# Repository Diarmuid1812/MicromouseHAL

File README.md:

# MicromouseHAL

1. Link do dokumentu Overleaf - Roboty Mobilne etap 2 (bez edycji)
   https://www.overleaf.com/read/mfgwrnbxdtrh
   
2. Link do dokumentu Overleaf - Sterowniki Robotów etap 2 (bez edycji)
   https://www.overleaf.com/read/fxndmzvgxdkn

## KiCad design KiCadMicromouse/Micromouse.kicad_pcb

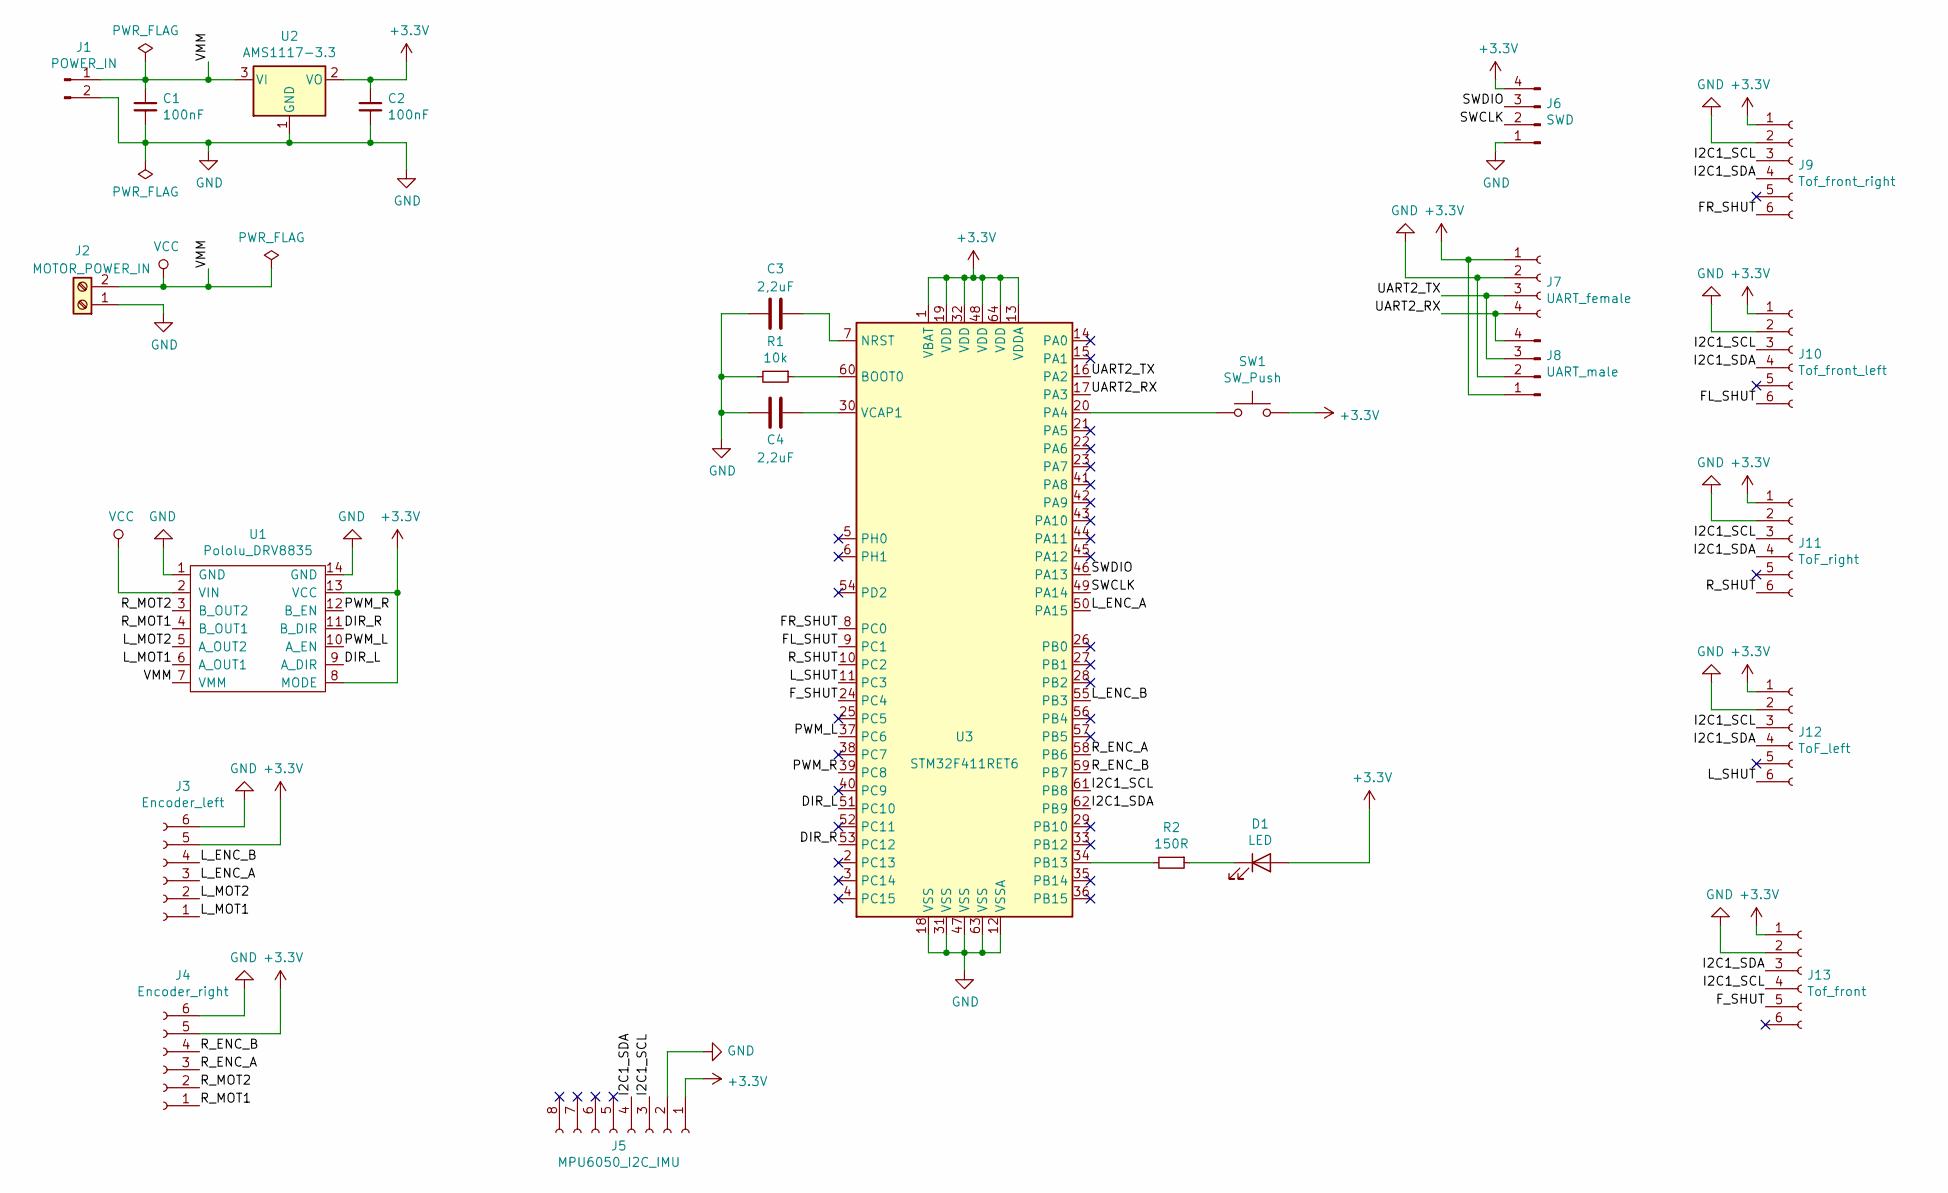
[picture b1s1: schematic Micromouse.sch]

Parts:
C1, C2: 100nF; C_1206_3216Metric
C3, C4: 2,2uF; C_1206_3216Metric
D1: LED; LED_D3.0mm
J1: POWER_IN; PinHeader_1x02_P2.54mm_Vertical
J2: MOTOR_POWER_IN; TerminalBlock_bornier-2_P5.08mm
J3: Encoder_left; PinSocket_1x06_P2.54mm_Vertical
J4: Encoder_right; PinSocket_1x06_P2.54mm_Vertical
J5: MPU6050_I2C_IMU; PinSocket_1x08_P2.54mm_Vertical
J6: SWD; PinHeader_1x04_P2.54mm_Vertical
J7: UART_female; PinSocket_1x04_P2.54mm_Vertical
J8: UART_male; PinHeader_1x04_P2.54mm_Vertical
J9: Tof_front_right; PinSocket_1x06_P2.54mm_Vertical
J10: Tof_front_left; PinSocket_1x06_P2.54mm_Vertical
J11: ToF_right; PinSocket_1x06_P2.54mm_Vertical
J12: ToF_left; PinSocket_1x06_P2.54mm_Vertical
J13: Tof_front; PinSocket_1x06_P2.54mm_Vertical
R1: 10k; R_1206_3216Metric
R2: 150R; R_1206_3216Metric
SW1: SW_Push; SW_SPST_TL3342
U1: Pololu_DRV8835; Pololu_DRV8835_rev
U2: AMS1117-3.3; SOT-223-3_TabPin2
U3: STM32F411RET6; LQFP-64_10x10mm_P0.5mm

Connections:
+3V3: C2.1, D1.2 (A), J3.5, J4.5, J5.1, J6.4, J7.1, J8.1, J9.1, J10.1, J11.1, J12.1, J13.1, SW1.2, U1.8 (MODE), U1.13 (VCC), U2.2 (VO), U3.1 (VBAT), U3.13 (VDDA), U3.19 (VDD), U3.32 (VDD), U3.48 (VDD), U3.64 (VDD)
/DIR_L: U1.9 (A_DIR), U3.51 (PC10)
/DIR_R: U1.11 (B_DIR), U3.53 (PC12)
/FL_SHUT: J10.6, U3.9 (PC1)
/FR_SHUT: J9.6, U3.8 (PC0)
/F_SHUT: J13.5, U3.24 (PC4)
/I2C1_SCL: J5.3, J9.3, J10.3, J11.3, J12.3, J13.4, U3.61 (PB8)
/I2C1_SDA: J5.4, J9.4, J10.4, J11.4, J12.4, J13.3, U3.62 (PB9)
/L_ENC_A: J3.3, U3.50 (PA15)
/L_ENC_B: J3.4, U3.55 (PB3)
/L_MOT1: J3.1, U1.6 (A_OUT1)
/L_MOT2: J3.2, U1.5 (A_OUT2)
/L_SHUT: J12.6, U3.11 (PC3)
/PWM_L: U1.10 (A_EN), U3.37 (PC6)
/PWM_R: U1.12 (B_EN), U3.39 (PC8)
/R_ENC_A: J4.3, U3.58 (PB6)
/R_ENC_B: J4.4, U3.59 (PB7)
/R_MOT1: J4.1, U1.4 (B_OUT1)
/R_MOT2: J4.2, U1.3 (B_OUT2)
/R_SHUT: J11.6, U3.10 (PC2)
/SWCLK: J6.2, U3.49 (PA14)
/SWDIO: J6.3, U3.46 (PA13)
/UART2_RX: J7.4, J8.4, U3.17 (PA3)
/UART2_TX: J7.3, J8.3, U3.16 (PA2)
GND: C1.2, C2.2, C3.2, C4.2, J1.2, J2.1, J3.6, J4.6, J5.2, J6.1, J7.2, J8.2, J9.2, J10.2, J11.2, J12.2, J13.2, R1.2, U1.1 (GND), U1.14 (GND), U2.1 (GND), U3.12 (VSSA), U3.18 (VSS), U3.31 (VSS), U3.47 (VSS), U3.63 (VSS)
unnamed: C3.1, U3.7 (NRST)
unnamed: C4.1, U3.30 (VCAP1)
unnamed: D1.1 (K), R2.1
unnamed: R1.1, U3.60 (BOOT0)
unnamed: R2.2, U3.34 (PB13)
unnamed: SW1.1, U3.20 (PA4)
VCC: C1.1, J1.1, J2.2, U1.2 (VIN), U1.7 (VMM), U2.3 (VI)

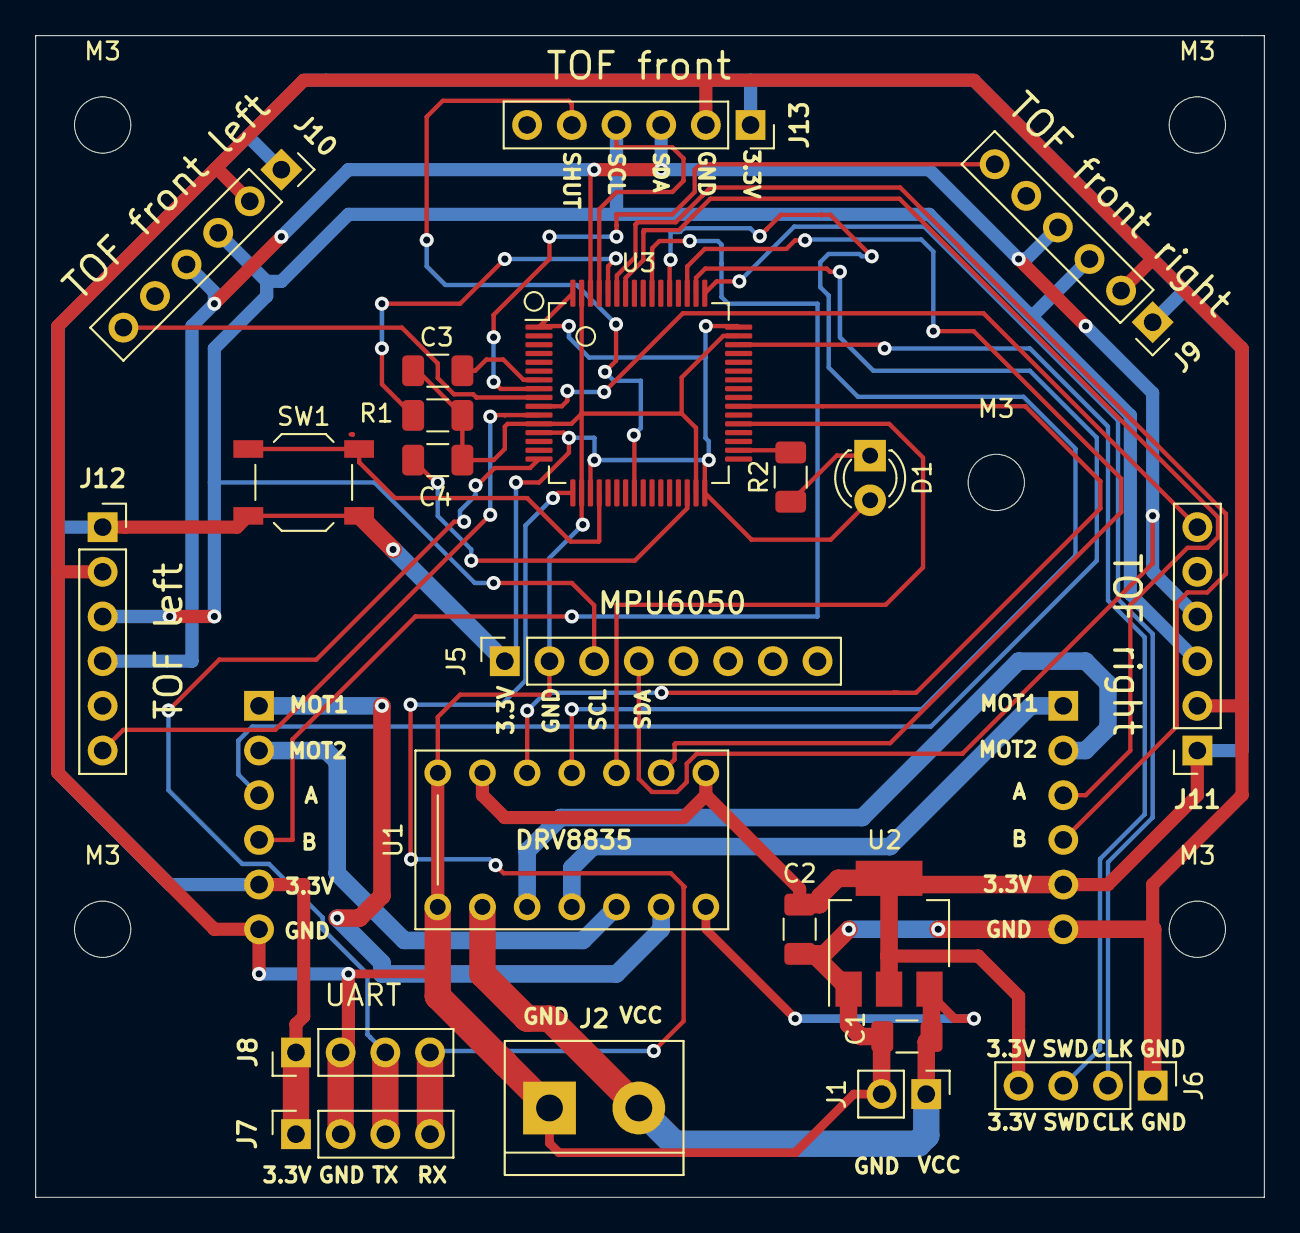
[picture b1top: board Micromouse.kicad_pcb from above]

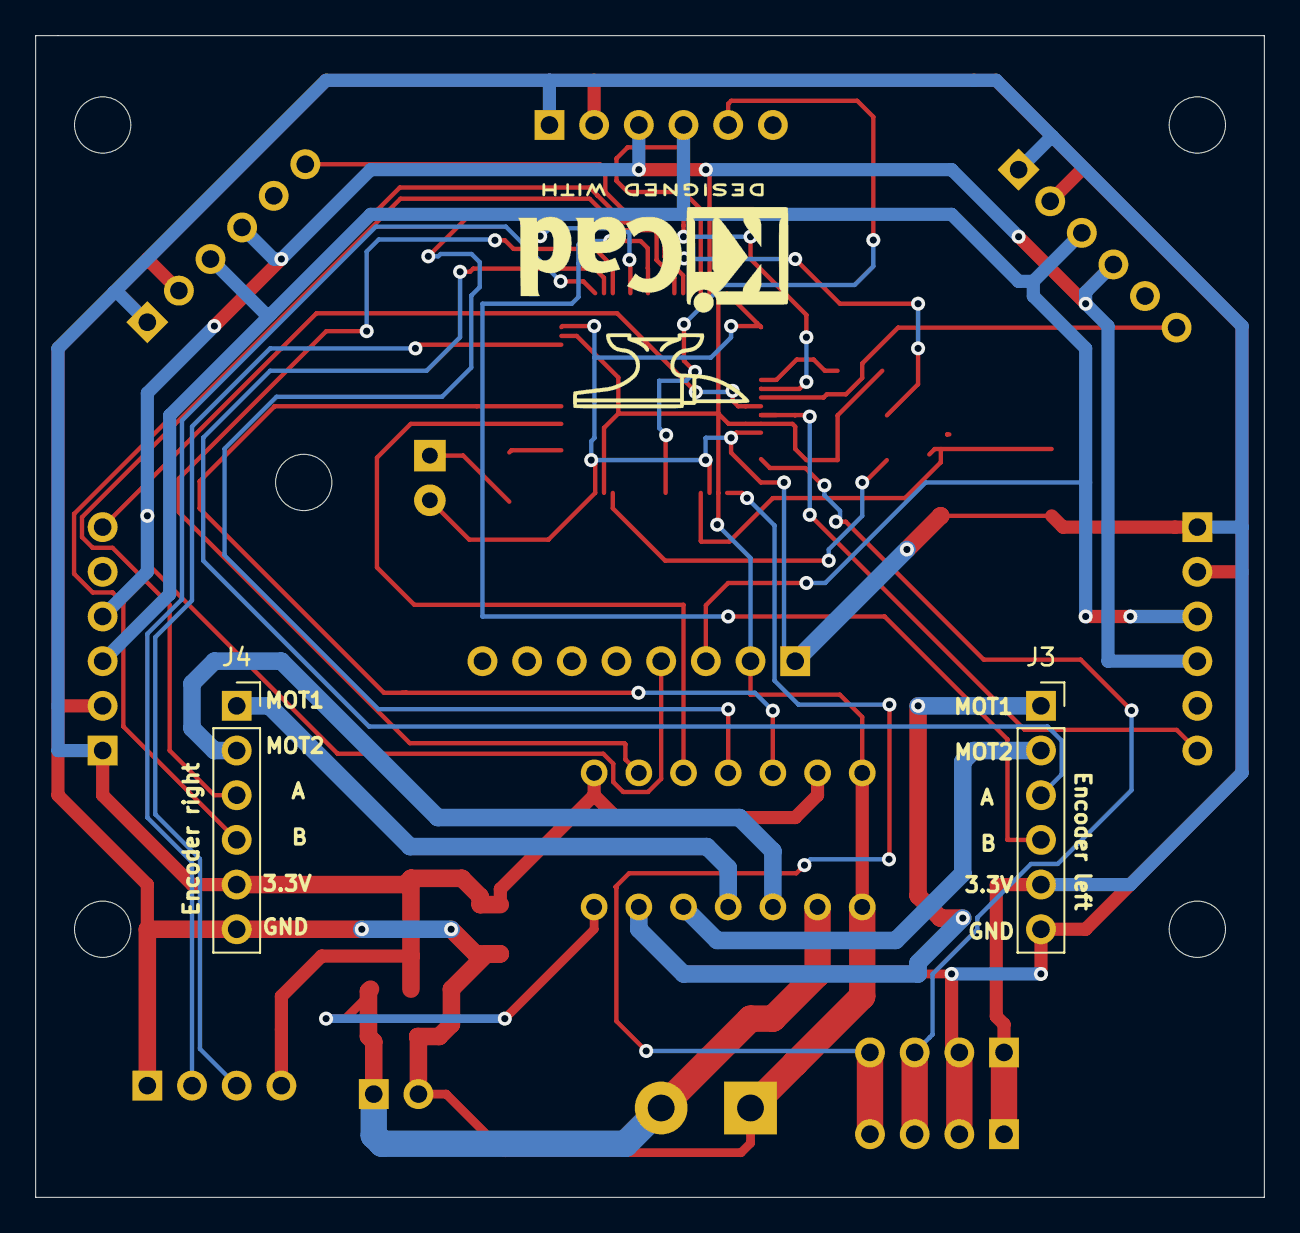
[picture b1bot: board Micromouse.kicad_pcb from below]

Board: 2 copper layers, 69.9 x 66.0 mm, 29 parts (2 on the bottom side), 32 nets.

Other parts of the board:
M3, M3#2, M3#3, M3#4, M3#5: MountingHole_3.2mm_M3

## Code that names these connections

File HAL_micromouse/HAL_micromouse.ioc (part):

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Mcu.Name=STM32F411R(C-E)Tx
Mcu.Package=LQFP64
Mcu.UserName=STM32F411RETx
PA13.GPIOParameters=GPIO_Label
PA13.GPIO_Label=TMS
PA13.Mode=Serial_Wire
PA13.Signal=SYS_JTMS-SWDIO
PA14.GPIOParameters=GPIO_Label
PA14.GPIO_Label=TCK
PA14.Mode=Serial_Wire
PA14.Signal=SYS_JTCK-SWCLK
PA15.GPIOParameters=GPIO_Label
PA15.GPIO_Label=ENC_L_A
PA15.Signal=S_TIM2_CH1_ETR
PA2.GPIOParameters=GPIO_Label
PA2.GPIO_Label=USART_TX
PA2.Mode=Asynchronous
PA2.Signal=USART2_TX
PA3.GPIOParameters=GPIO_Label
PA3.GPIO_Label=USART_RX
PA3.Mode=Asynchronous
PA3.Signal=USART2_RX
PA4.GPIOParameters=GPIO_PuPd,GPIO_Label
PA4.GPIO_Label=BUTTON
PA4.GPIO_PuPd=GPIO_PULLDOWN
PA4.Signal=GPIO_Input
PB13.GPIOParameters=GPIO_Label
PB13.GPIO_Label=RED_LED
PB13.Signal=GPIO_Output
PB3.GPIOParameters=GPIO_Label
PB3.GPIO_Label=ENC_L_B
PB3.Signal=S_TIM2_CH2
PB6.GPIOParameters=GPIO_Label
PB6.GPIO_Label=ENC_R_A
PB6.Signal=S_TIM4_CH1
PB7.GPIOParameters=GPIO_Label
PB7.GPIO_Label=ENC_R_B
PB7.Signal=S_TIM4_CH2
PB8.GPIOParameters=GPIO_Label
PB8.GPIO_Label=I2C1_SCL
PB8.Mode=I2C
PB8.Signal=I2C1_SCL
PB9.GPIOParameters=GPIO_Label
PB9.GPIO_Label=I2C1_SDA
PB9.Mode=I2C
PB9.Signal=I2C1_SDA
PC0.GPIOParameters=GPIO_Label
PC0.GPIO_Label=TOF_GPIO_FR
PC0.Signal=GPIO_Output
PC1.GPIOParameters=GPIO_Label
PC1.GPIO_Label=TOF_GPIO_FL
PC1.Signal=GPIO_Output
PC10.GPIOParameters=GPIO_Label
PC10.GPIO_Label=DIR_L
PC10.Signal=GPIO_Output
PC12.GPIOParameters=GPIO_Label
PC12.GPIO_Label=DIR_R
PC12.Signal=GPIO_Output
PC13-ANTI_TAMP.GPIOParameters=GPIO_Label,GPIO_ModeDefaultEXTI
PC13-ANTI_TAMP.GPIO_Label=B1 [Blue PushButton]
PC13-ANTI_TAMP.GPIO_ModeDefaultEXTI=GPIO_MODE_IT_FALLING
PC13-ANTI_TAMP.Signal=GPXTI13
PC2.GPIOParameters=GPIO_Label
PC2.GPIO_Label=TOF_GPIO_R
PC2.Signal=GPIO_Output
PC3.GPIOParameters=GPIO_Label
PC3.GPIO_Label=TOF_GPIO_L
PC3.Signal=GPIO_Output
PC4.GPIOParameters=GPIO_Label
PC4.GPIO_Label=TOF_GPIO_F
PC4.Signal=GPIO_Output
PC6.GPIOParameters=GPIO_Label
PC6.GPIO_Label=PWML
PC6.Signal=S_TIM3_CH1
PC8.GPIOParameters=GPIO_Label
PC8.GPIO_Label=PWMR
PC8.Signal=S_TIM3_CH3
RCC.HSE_VALUE=8000000
RCC.SYSCLKFreq_VALUE=84000000
RCC.SYSCLKSource=RCC_SYSCLKSOURCE_PLLCLK
board=NUCLEO-F411RE
boardIOC=true

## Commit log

2020-04-20 Test enkoderów
    Konfiguracja enkoderów i odczyt danych z enkoderów w kodzie
2020-04-22 Enkodery, ruch - brak konfiguracji
    Zamknięcie obsługi enkoderów w funkcje i dodanie funkcji obsługujących najprostsze ruchy.
    Brak konfiguracji umożliwiającej przerprowadzenie testówm do uporządkowania po konfiguracji
2020-04-23 Prosta reprezentacja mapy
2020-05-02 Wersja bazowa do rozwoju
    + generowanie kodu z Cube jako osobnych par plików .c/.h dla każdego peryferium
    + ostateczna konfiguracja peryferiów w Cube
    + działające funkcje kontroli silników
    + działający odczyt danych z MPU6050
    + działający odczyt danych z enkoderów
    + biblioteka HAL dla VL53L0x, działające odczyty i zapisy do rejestrów
2020-05-03 Przekierowanie printf() na port szeregowy
    + Przekierowanie funkcji printf() na USART2, 115200 baudrate
2020-05-04 Dodanie funkcji liczących CRC32 i generujących ramkę z danymi z czujników
    + dodanie funkcji wyliczających crc32 dla dowolnej tablicy bajtów
    + dodanie funkcji tworzącej ramkę danych z odczytami z czujników
2020-05-06 Działające czujniki VL53L0x
    + skuteczna biblioteka dla VL53l0x
    Odczyty są prawidłowe, funkcje ToF_writeMulti() i ToF_readMulti() wysyłają/zwracają nie to, co do nich przekazano, tylko to co powinny. Wartości są wpisane na stałe. Jak komuś się chce to może to pop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
2020-05-07 Projekt elektroniki w KiCad
    +dodano projekt elektroniki z programu KiCad w folderze KiCadMicromouse
    +usunięto nieużywany projekt CubeIDE ze wstępną konfiguracją peryferiów
2020-05-08 Linki do podglądu sprawozdań w Overleaf
    + w pliku README.md dodano linki do podglądu dokumentów w Overleaf
2020-05-10 Projekt 3D w Blenderze
    + Dodano plik Blendera zawierający elementy do wydruku i scenę do renderowania modelu robota
2020-05-11 Dodanie .gitignore, poprawienie błędu w VL53L0x.c
    +dodano plik .gitignore do repozytorium. Ignorowany jest katalog HAL_micromouse/Debug i pliki zapasowe KiCad.
    +poprawiono błąd w funkcji ToF_readMulti()
    +usunięto ścieżki nieużywanych bibliotek
2020-05-14 Prototyp Flood Fill
2020-05-22 Filtr medianowy dla czujników ToF
    +dodano filtr medianowy dla odczytów odległości z czujników ToF. Skutecznie odrzuca pojawiającą się czasami pomimo obecności przeszkody wartość 8191 oznaczającą przekroczenie zakresu.
2020-05-23 Regulator PID - jazda do przodu
    + uruchomienie TIM10 dla regulatora PID
    + dodanie makr do obsługi diody LED
    + wstępne nastawy PID
    + poprawienie błędu resetowania enkoderów
2020-05-24 Ruchy na wprost o zadaną odległość z PID
    + umieszczenie regulatora PID w pliku move.c w funkcjach odpowiedzialnych za ruch do przodu i do tyłu
    + uzupełnienie funkcji ruchu o dystans i prędkość
    + funkcje ruchu działają teraz nieblokująco, po wywołaniu wyzwalają ruch, a potem sprawdzają, czy już się skończył. Zwracają wartość 0 lub 1 zależnie od wartości enkoderów. Po zakończeniu resetują st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
    + dodano makro do obsługi przycisku
    + przeorganizowano pliki pid.c i pid.h
2020-05-25 PID obiektowo
2020-05-26 Rotacja robota oparta o żyroskop
    + pomiar rotacji w oparciu o żyroskop
    + funkcje obrotu w prawo i w lewo o zadany kąt. Działają bardzo precyzyjnie dla kątów większych niż kilkanaście stopni, z prędkością silników 100
    +funkcja obrotu z regulatorem PID. Wymaga poprawy nastaw, wykazuje długo gasnące oscylacje w końcowej fazie stabilizacji
    + zmiana z PID ISA na PID IND -wzmocnienie członu proporcjonalnego nie wpływa na wzmocnienia innych członów
    +instancje struktur PID umieszczone w pliku move.h
2020-05-30 Windup dla członu I regulatora PID
    +dodano windup członu I - zabezpieczenie przez nieograniczonym narastaniem całki
    +dobrano parametry regulatora PID dla obrotu. Funkcja bez PID wciąż działa nieco lepiej, ale z PID jest już ok
2020-06-10 Test ruchu
2020-06-10 Wykrywanie ścian
2020-06-10 Sprawdzanie ścian i wybieranie kierunku w FloodFill
2020-06-11 Ruch w labiryncie
2020-06-11 Popraione warunki w FloodFill
2020-06-11 Inkrementacja pozycji robota w labirynice
2020-06-11 Uporzdkowanie zmiennych FloodFill
2020-06-11 Sygnalizacja błędów
2020-06-12 Drobne poprawki ruchów
